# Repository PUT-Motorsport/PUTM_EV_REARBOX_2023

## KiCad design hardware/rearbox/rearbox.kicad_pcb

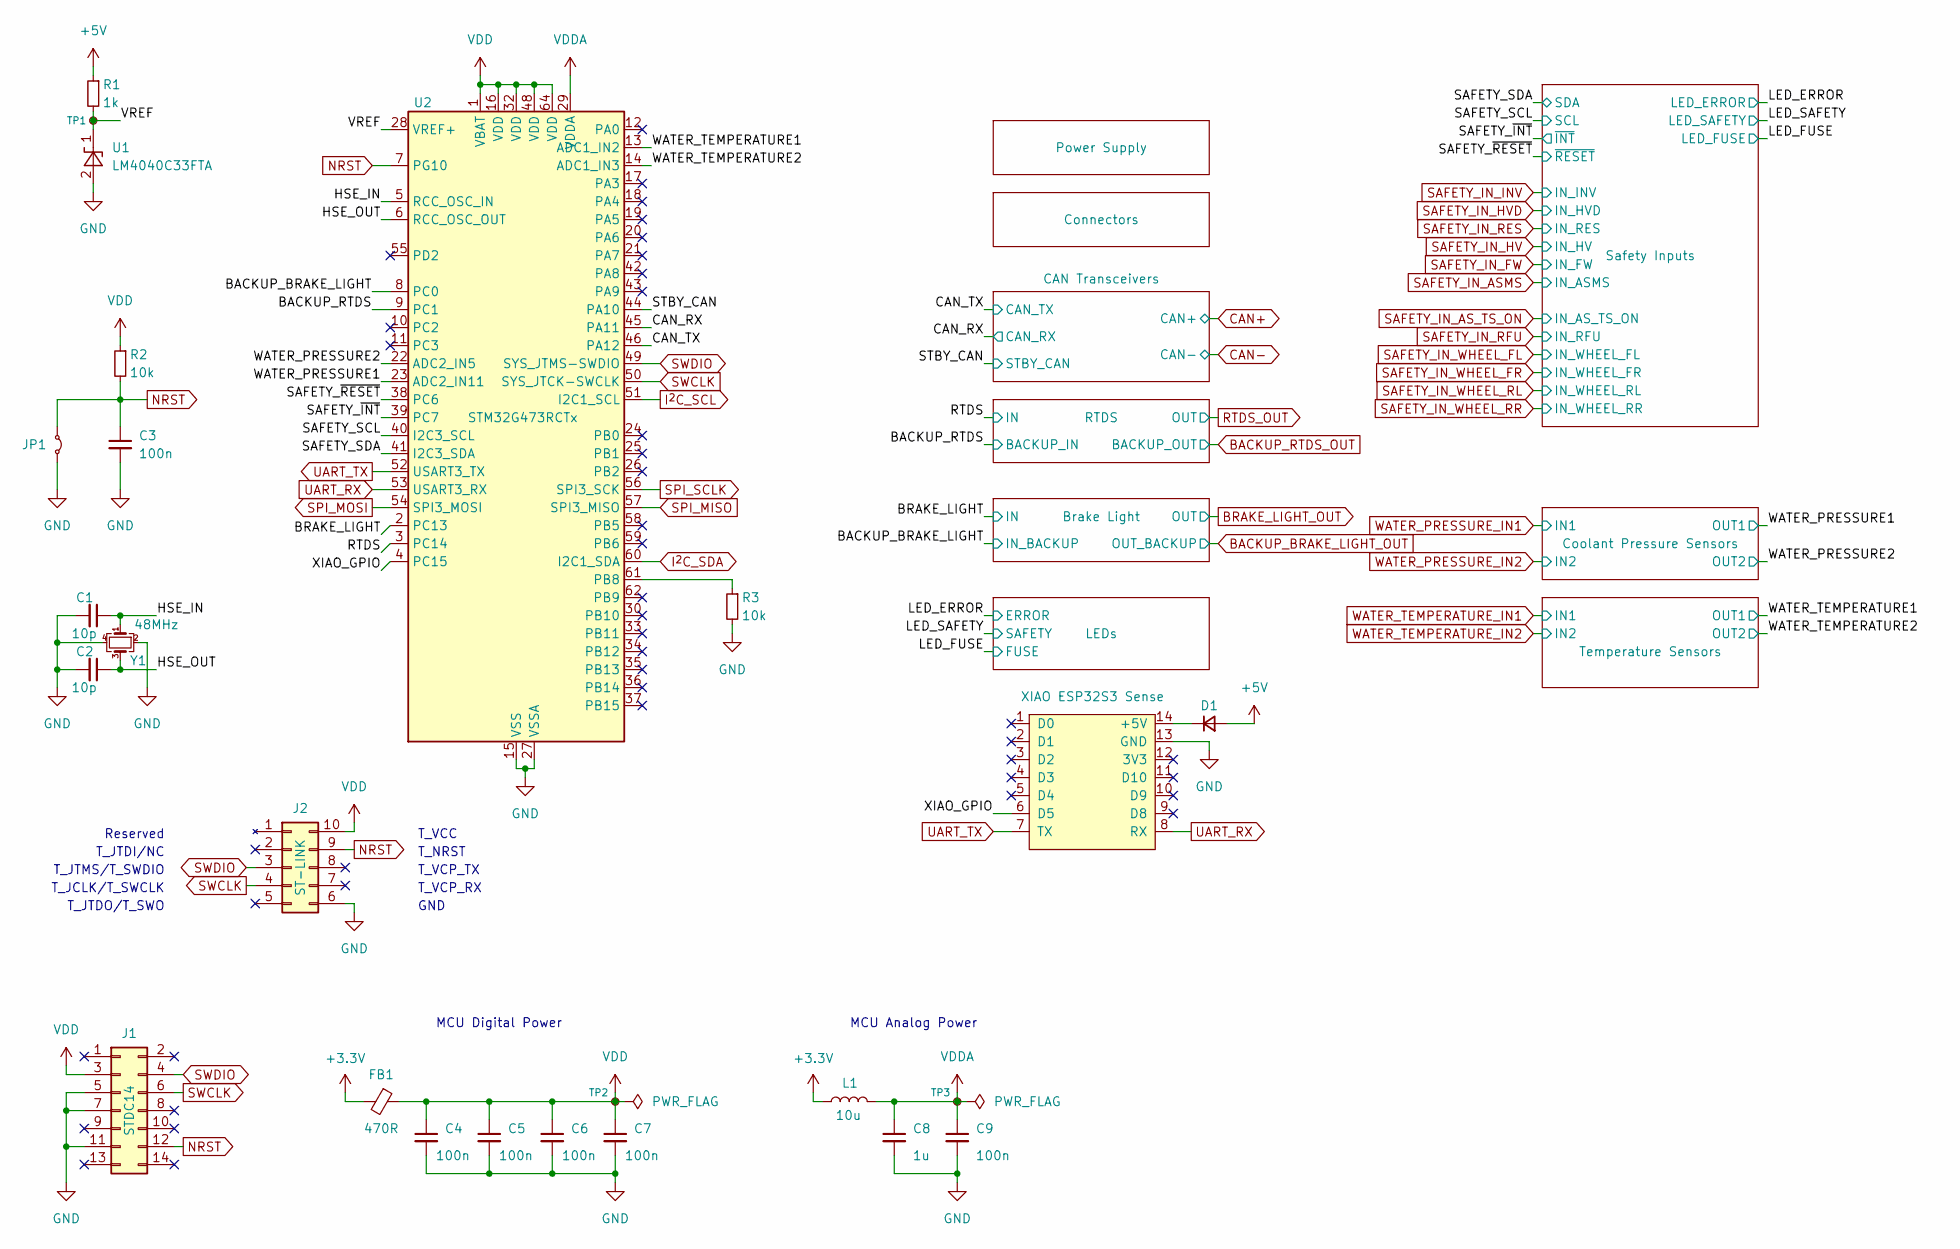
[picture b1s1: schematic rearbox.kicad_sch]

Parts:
C1, C2: 10p; C_0603_1608Metric
C3, C4, C5, C6, C7, C9: 100n; C_0603_1608Metric
C8: 1u; C_0603_1608Metric
D1: NSVRB751V40T1G; D_SOD-323_HandSoldering; Mouser Part Number 863-NSVRB751V40T1G
FB1: 470R; L_0603_1608Metric
J1: STDC14; PinHeader_2x07_P1.27mm_Vertical_SMD
J2: ST-LINK; STLINK-V3MINIE
J5: XIAO ESP32S3 Sense; XIAO-ESP32S3-DIP
JP1: Jumper_2_Small_Bridged; SolderJumper-2_P1.3mm_Open_TrianglePad1.0x1.5mm
L1: 10u; L_0603_1608Metric
R1: 1k; R_0603_1608Metric
R2, R3: 10k; R_0603_1608Metric
TP1, TP2, TP3: TestPoint_Small; TestPoint_Pad_D1.0mm
U1: LM4040C33FTA; SOT-23
U2: STM32G473RCTx; LQFP-64_10x10mm_P0.5mm
Y1: 48MHz; Crystal_SMD_Abracon_ABM8G-4Pin_3.2x2.5mm

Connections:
+3.3V: FB1.2, L1.1; also elsewhere on the board
+5V: D1.2 (A), R1.1; also elsewhere on the board
/BACKUP_BRAKE_LIGHT: U2.8 (PC0); also elsewhere on the board
/BACKUP_RTDS: U2.9 (PC1); also elsewhere on the board
/BRAKE_LIGHT: U2.2 (PC13); also elsewhere on the board
/CAN_RX: U2.45 (PA11); also elsewhere on the board
/CAN_TX: U2.46 (PA12); also elsewhere on the board
/HSE_IN: C1.1, U2.5 (RCC_OSC_IN), Y1.1
/HSE_OUT: C2.1, U2.6 (RCC_OSC_OUT), Y1.3
/RTDS: U2.3 (PC14); also elsewhere on the board
/SAFETY_SCL: U2.40 (I2C3_SCL); also elsewhere on the board
/SAFETY_SDA: U2.41 (I2C3_SDA); also elsewhere on the board
/SAFETY_~INT: U2.39 (PC7); also elsewhere on the board
/SAFETY_~RESET: U2.38 (PC6); also elsewhere on the board
/STBY_CAN: U2.44 (PA10); also elsewhere on the board
/VREF: R1.2, TP1.1, U1.1 (K), U2.28 (VREF+)
/WATER_PRESSURE1: U2.23 (ADC2_IN11); also elsewhere on the board
/WATER_PRESSURE2: U2.22 (ADC2_IN5); also elsewhere on the board
/WATER_TEMPERATURE1: U2.13 (ADC1_IN2); also elsewhere on the board
/WATER_TEMPERATURE2: U2.14 (ADC1_IN3); also elsewhere on the board
/XIAO_GPIO: J5.6 (D5), U2.4 (PC15)
GND: C1.2, C2.2, C3.2, C4.2, C5.2, C6.2, C7.2, C8.2, C9.2, J1.5, J1.7, J1.11, J2.6 (GND), J5.13 (GND), JP1.2 (B), R3.2, U1.2 (A), U2.15 (VSS), U2.27 (VSSA), U2.31 (VSS), U2.47 (VSS), U2.63 (VSS), Y1.2, Y1.4; also elsewhere on the board
I^{2}C_SCL: U2.51 (I2C1_SCL); also elsewhere on the board
I^{2}C_SDA: U2.60 (I2C1_SDA); also elsewhere on the board
NRST: C3.1, J1.12, J2.9 (T_NRST), JP1.1 (A), R2.2, U2.7 (PG10)
unnamed: D1.1 (K), J5.14 (+5V)
unnamed: R3.1, U2.61 (PB8)
SPI_MISO: U2.57 (SPI3_MISO); also elsewhere on the board
SPI_MOSI: U2.54 (SPI3_MOSI); also elsewhere on the board
SPI_SCLK: U2.56 (SPI3_SCK); also elsewhere on the board
SWCLK: J1.6, J2.4 (T_JCLK/T_SWCLK), U2.50 (SYS_JTCK-SWCLK)
SWDIO: J1.4, J2.3 (T_JTMS/T_SWDIO), U2.49 (SYS_JTMS-SWDIO)
UART_RX: J5.8 (RX), U2.53 (USART3_RX); also elsewhere on the board
UART_TX: J5.7 (TX), U2.52 (USART3_TX); also elsewhere on the board
VDD: C4.1, C5.1, C6.1, C7.1, FB1.1, J1.3, J2.10 (T_VCC), R2.1, TP2.1, U2.1 (VBAT), U2.16 (VDD), U2.32 (VDD), U2.48 (VDD), U2.64 (VDD)
VDDA: C8.1, C9.1, L1.2, TP3.1, U2.29 (VDDA)

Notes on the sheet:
T_JCLK/T_SWCLK
T_JTMS/T_SWDIO
MCU Analog Power
T_JTDI/NC
T_VCC
T_JTDO/T_SWO
T_NRST
Reserved
T_VCP_RX
T_VCP_TX
GND
MCU Digital Power

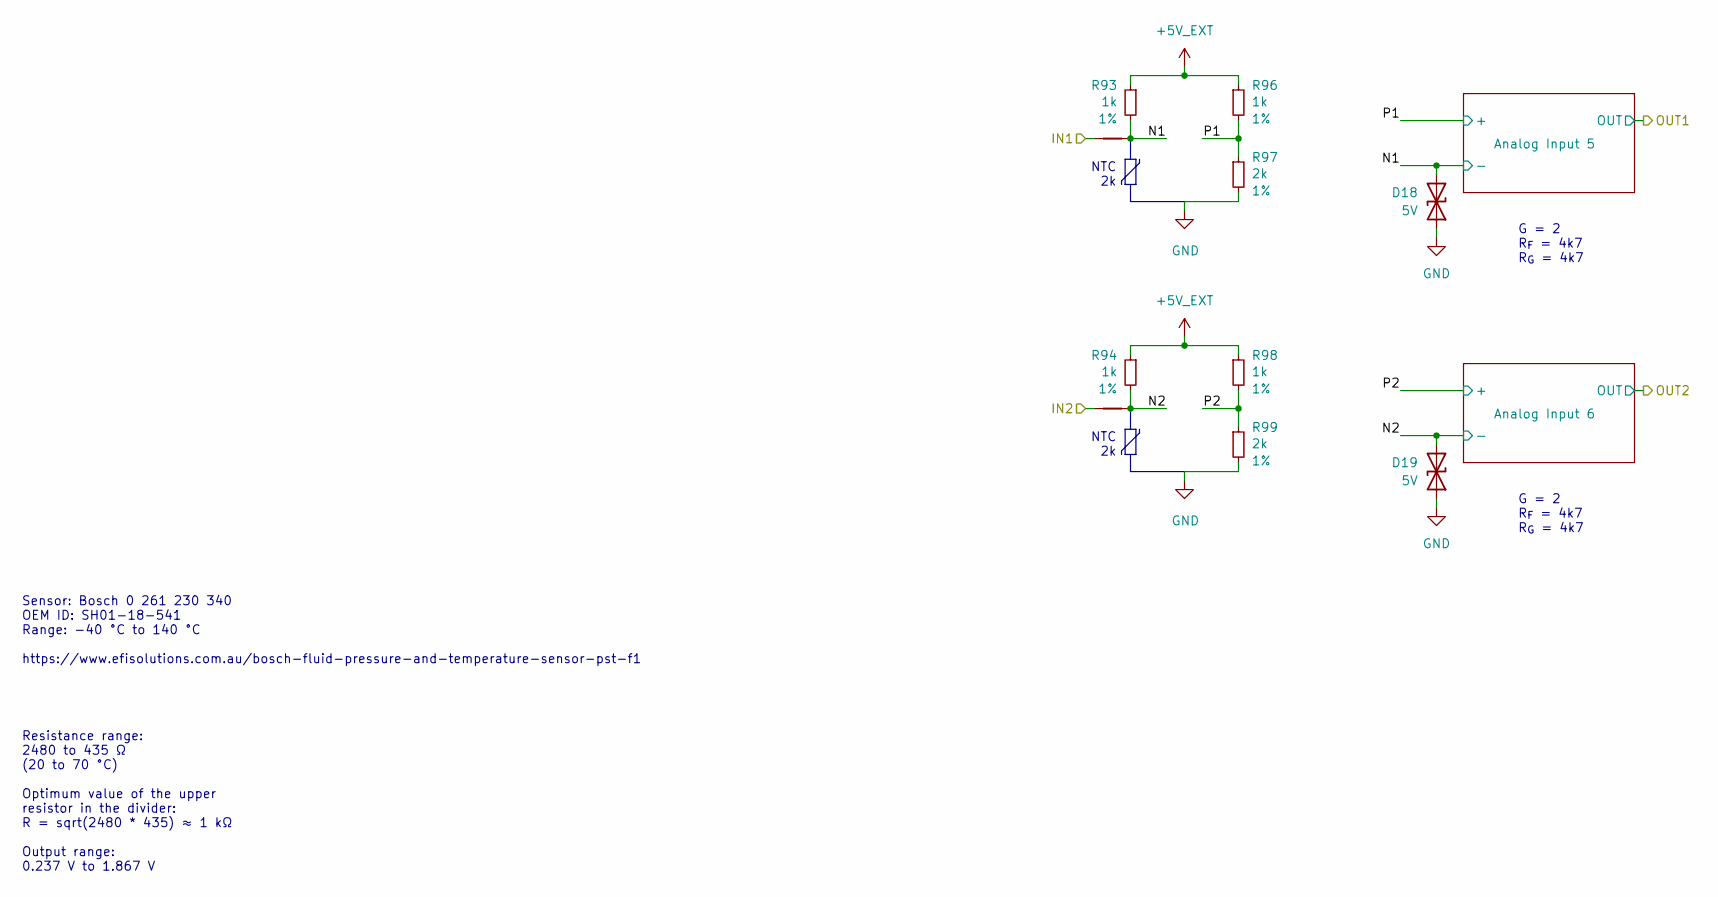
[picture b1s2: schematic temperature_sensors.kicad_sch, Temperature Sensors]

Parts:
D18, D19: 5V; D_SOD-523
NT1, NT2: NetTie_2; NetTie-2_SMD_Pad0.2mm
R93, R94, R96, R98: 1k; R_0603_1608Metric; Tolerance 1%
R97, R99: 2k; R_0603_1608Metric; Tolerance 1%

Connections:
+5V_EXT: R93.1, R94.1, R96.1, R98.1; also elsewhere on the board
/Temperature Sensors/N1: D18.2 (A2), NT1.2, R93.2; also elsewhere on the board
/Temperature Sensors/N2: D19.2 (A2), NT2.2, R94.2; also elsewhere on the board
/Temperature Sensors/P1: R96.2, R97.1; also elsewhere on the board
/Temperature Sensors/P2: R98.2, R99.1; also elsewhere on the board
GND: D18.1 (A1), D19.1 (A1), R97.2, R99.2; also elsewhere on the board
WATER_TEMPERATURE_IN1: NT1.1; also elsewhere on the board
WATER_TEMPERATURE_IN2: NT2.1; also elsewhere on the board

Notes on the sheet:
G = 2 R_{F} = 4k7 R_{G} = 4k7
NTC 2k
Resistance range: 2480 to 435 Ω (20 to 70 °C) Optimum value of the upper resistor in the divider: R = sqrt(2480 * 435) ≈ 1 kΩ Output range: 0.237 V to 1.867 V
Sensor: Bosch 0 261 230 340 OEM ID: SH01-18-541 Range: -40 °C to 140 °C https://www.efisolutions.com.au/bosch-fluid-pressure-and-temperature-sensor-pst-f1

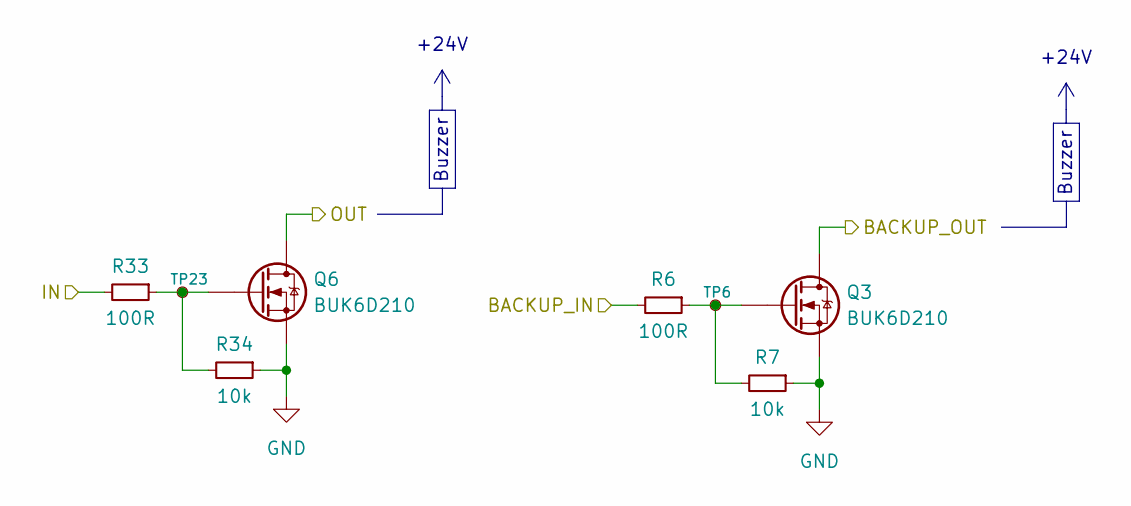
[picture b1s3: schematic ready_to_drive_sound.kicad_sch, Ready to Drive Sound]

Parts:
Q3, Q6: BUK6D210; Diodes_UDFN2020-6_Type-F
R6, R33: 100R; R_0603_1608Metric
R7, R34: 10k; R_0603_1608Metric
TP6, TP23: TestPoint_Small; TestPoint_Pad_D1.0mm

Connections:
/BACKUP_RTDS: R6.2; also elsewhere on the board
/RTDS: R33.2; also elsewhere on the board
BACKUP_RTDS_OUT: Q3.1 (D), Q3.2 (D), Q3.5 (D), Q3.6 (D), Q3.7 (D); also elsewhere on the board
GND: Q3.4 (S), Q3.8 (S), Q6.4 (S), Q6.8 (S), R7.1, R34.1; also elsewhere on the board
unnamed: Q3.3 (G), R6.1, R7.2, TP6.1
unnamed: Q6.3 (G), R33.1, R34.2, TP23.1
RTDS_OUT: Q6.1 (D), Q6.2 (D), Q6.5 (D), Q6.6 (D), Q6.7 (D); also elsewhere on the board

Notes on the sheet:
+24V
Buzzer

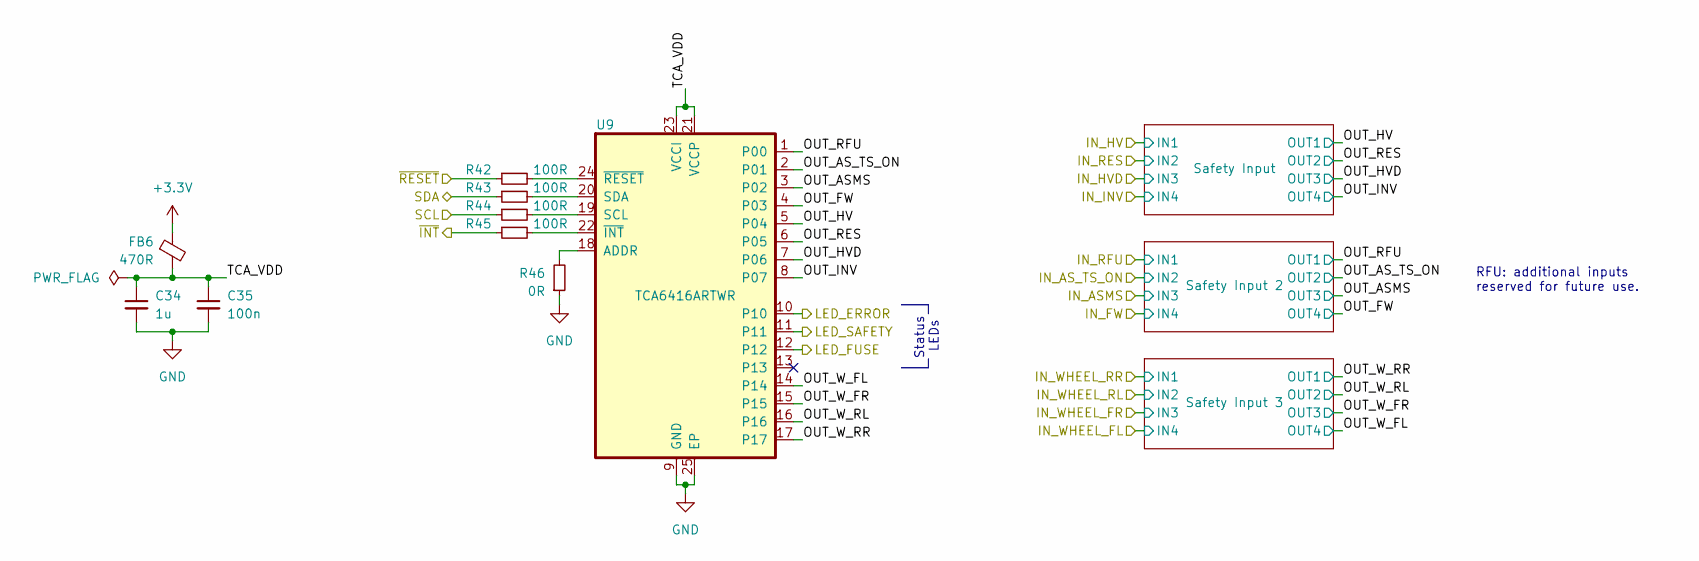
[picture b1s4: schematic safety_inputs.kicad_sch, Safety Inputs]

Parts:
C34: 1u; C_0603_1608Metric
C35: 100n; C_0603_1608Metric
FB6: 470R; L_0603_1608Metric
R42, R43, R44, R45: 100R; R_0603_1608Metric
R46: 0R; R_0603_1608Metric
U9: TCA6416ARTWR; QFN50P400X400X80-25N

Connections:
+3.3V: FB6.1; also elsewhere on the board
/LED_ERROR: U9.10; also elsewhere on the board
/LED_FUSE: U9.12; also elsewhere on the board
/LED_SAFETY: U9.11; also elsewhere on the board
/SAFETY_SCL: R44.1; also elsewhere on the board
/SAFETY_SDA: R43.1; also elsewhere on the board
/SAFETY_~INT: R45.1; also elsewhere on the board
/SAFETY_~RESET: R42.1; also elsewhere on the board
/Safety Inputs/OUT_ASMS: U9.3 (P02); also elsewhere on the board
/Safety Inputs/OUT_AS_TS_ON: U9.2 (P01); also elsewhere on the board
/Safety Inputs/OUT_FW: U9.4 (P03); also elsewhere on the board
/Safety Inputs/OUT_HV: U9.5 (P04); also elsewhere on the board
/Safety Inputs/OUT_HVD: U9.7 (P06); also elsewhere on the board
/Safety Inputs/OUT_INV: U9.8 (P07); also elsewhere on the board
/Safety Inputs/OUT_RES: U9.6 (P05); also elsewhere on the board
/Safety Inputs/OUT_RFU: U9.1 (P00); also elsewhere on the board
/Safety Inputs/OUT_W_FL: U9.14; also elsewhere on the board
/Safety Inputs/OUT_W_FR: U9.15; also elsewhere on the board
/Safety Inputs/OUT_W_RL: U9.16; also elsewhere on the board
/Safety Inputs/OUT_W_RR: U9.17; also elsewhere on the board
/Safety Inputs/TCA_VDD: C34.1, C35.1, FB6.2, U9.21 (VCCP), U9.23 (VCCI)
GND: C34.2, C35.2, R46.1, U9.9 (GND), U9.25 (EP); also elsewhere on the board
unnamed: R46.2, U9.18 (ADDR)
unnamed: R44.2, U9.19 (SCL)
unnamed: R43.2, U9.20 (SDA)
unnamed: R45.2, U9.22 (~INT)
unnamed: R42.2, U9.24 (~RESET)

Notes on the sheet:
Status LEDs
RFU: additional inputs reserved for future use.

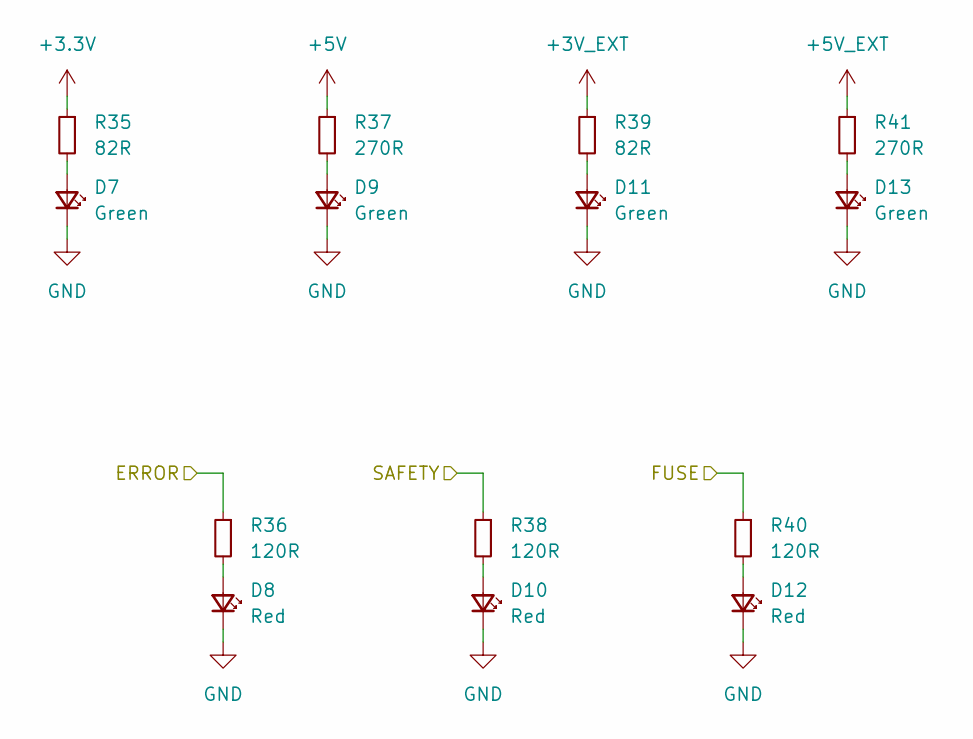
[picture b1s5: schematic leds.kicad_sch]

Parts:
D7, D9, D11, D13: Green; LED_0603_1608Metric
D8, D10, D12: Red; LED_0603_1608Metric
R35, R39: 82R; R_0603_1608Metric
R36, R38, R40: 120R; R_0603_1608Metric
R37, R41: 270R; R_0603_1608Metric

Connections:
+3.3V: R35.1; also elsewhere on the board
+3V_EXT: R39.1; also elsewhere on the board
+5V: R37.1; also elsewhere on the board
+5V_EXT: R41.1; also elsewhere on the board
/LED_ERROR: R36.1; also elsewhere on the board
/LED_FUSE: R40.1; also elsewhere on the board
/LED_SAFETY: R38.1; also elsewhere on the board
GND: D7.1 (K), D8.1 (K), D9.1 (K), D10.1 (K), D11.1 (K), D12.1 (K), D13.1 (K); also elsewhere on the board
unnamed: D7.2 (A), R35.2
unnamed: D8.2 (A), R36.2
unnamed: D9.2 (A), R37.2
unnamed: D10.2 (A), R38.2
unnamed: D11.2 (A), R39.2
unnamed: D12.2 (A), R40.2
unnamed: D13.2 (A), R41.2

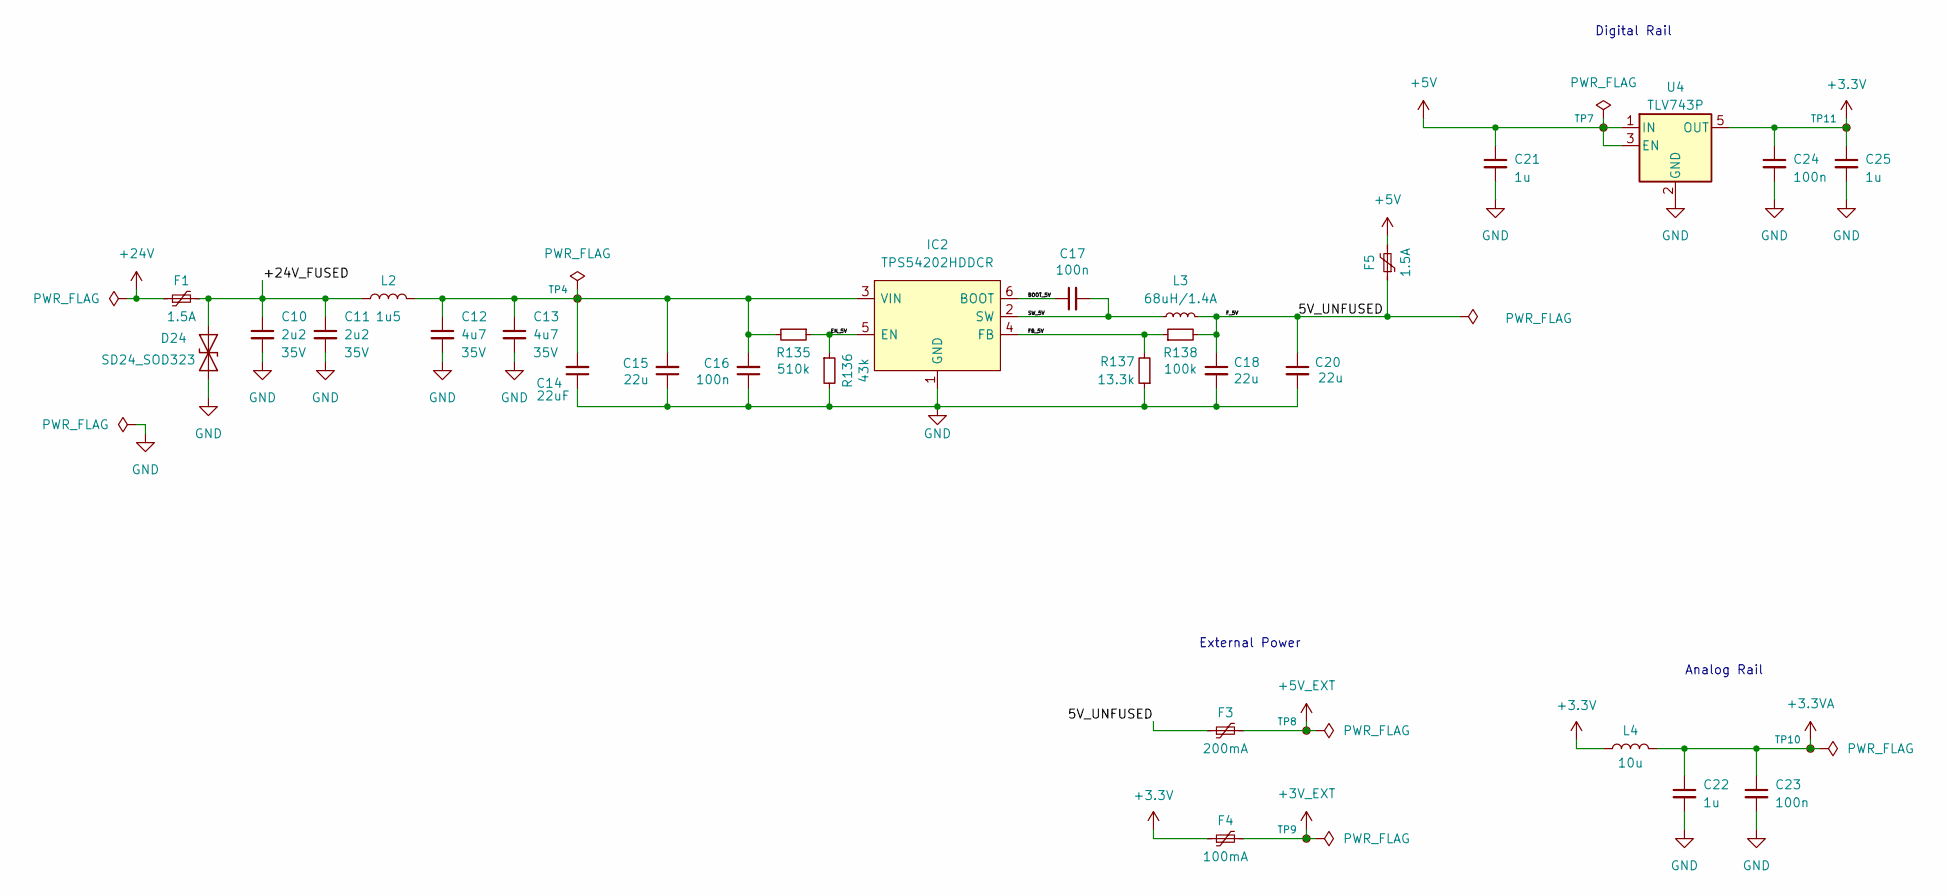
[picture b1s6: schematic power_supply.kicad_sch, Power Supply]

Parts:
C10, C11: 2u2; C_0805_2012Metric; Rated Voltage 35V
C12, C13: 4u7; C_0805_2012Metric; Rated Voltage 35V
C14: 22uF; C_0805_2012Metric; Manufacturer_Part_Number CL21A107MQYNNWE; Mouser Part Number 810-C2012X5R1V226MAC
C15, C18, C20: 22u; C_0805_2012Metric; Manufacturer_Part_Number CL21A107MQYNNWE; Mouser Part Number 810-C2012X5R1V226MAC
C16, C17: 100n; C_0603_1608Metric; Manufacturer_Part_Number C0603C104J3RACTU; Mouser Part Number --
C21, C22, C25: 1u; C_0603_1608Metric
C23, C24: 100n; C_0603_1608Metric
D24: SD24_SOD323; D_SOD-323
F1, F5: 1.5A; Fuse_1812_4532Metric
F3: 200mA; Fuse_1812_4532Metric
F4: 100mA; Fuse_1812_4532Metric
IC2: TPS54202HDDCR; SOT-23-6; Mouser Part Number 595-TPS54202HDDCR
L2: 1u5; L_Abracon_ASPI-4030S
L3: 68uH/1.4A; L_TDK_VLS6045EX_VLS6045AF; Mouser Part Number 810-VLS6045EX-680M
L4: 10u; L_0603_1608Metric
R135: 510k; R_0603_1608Metric; Manufacturer_Part_Number RT0603DRD07510KL; Mouser Part Number 603-RT0603DRD07510KL
R136: 43k; R_0603_1608Metric; Manufacturer_Part_Number RT0603DRD07510KL; Mouser Part Number 603-RT0603DRD07510KL
R137: 13.3k; R_0603_1608Metric; Manufacturer_Part_Number RT0603DRE0713K3L; Mouser Part Number 603-RT0603DRE0713K3L
R138: 100k; R_0603_1608Metric; Manufacturer_Part_Number RT0603DRE07100KL; Mouser Part Number --
TP4, TP7, TP8, TP9, TP10, TP11: TestPoint_Small; TestPoint_Pad_D1.0mm
U4: TLV743P; SOT-23-5

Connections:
+3.3V: C24.1, C25.1, F4.1, L4.1, TP11.1, U4.5 (OUT); also elsewhere on the board
+3.3VA: C22.1, C23.1, L4.2, TP10.1; also elsewhere on the board
+3V_EXT: F4.2, TP9.1; also elsewhere on the board
+5V: C21.1, F5.2, TP7.1, U4.1 (IN), U4.3 (EN); also elsewhere on the board
+5V_EXT: F3.2, TP8.1; also elsewhere on the board
+24V: F1.1; also elsewhere on the board
/Power Supply/5V_UNFUSED: C18.1, C20.1, F3.1, F5.1, L3.2, R138.2
/Power Supply/+24V_FUSED: C10.1, C11.1, D24.2 (A2), F1.2, L2.1
/Power Supply/BOOT_5V: C17.1, IC2.6 (BOOT)
/Power Supply/EN_5V: IC2.5 (EN), R135.1, R136.1
/Power Supply/FB_5V: IC2.4 (FB), R137.2, R138.1
/Power Supply/SW_5V: C17.2, IC2.2 (SW), L3.1
GND: C10.2, C11.2, C12.2, C13.2, C14.1, C15.1, C16.1, C18.2, C20.2, C21.2, C22.2, C23.2, C24.2, C25.2, D24.1 (A1), IC2.1 (GND), R136.2, R137.1, U4.2 (GND); also elsewhere on the board
unnamed: C12.1, C13.1, C14.2, C15.2, C16.2, IC2.3 (VIN), L2.2, R135.2, TP4.1

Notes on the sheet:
Analog Rail
Digital Rail
External Power

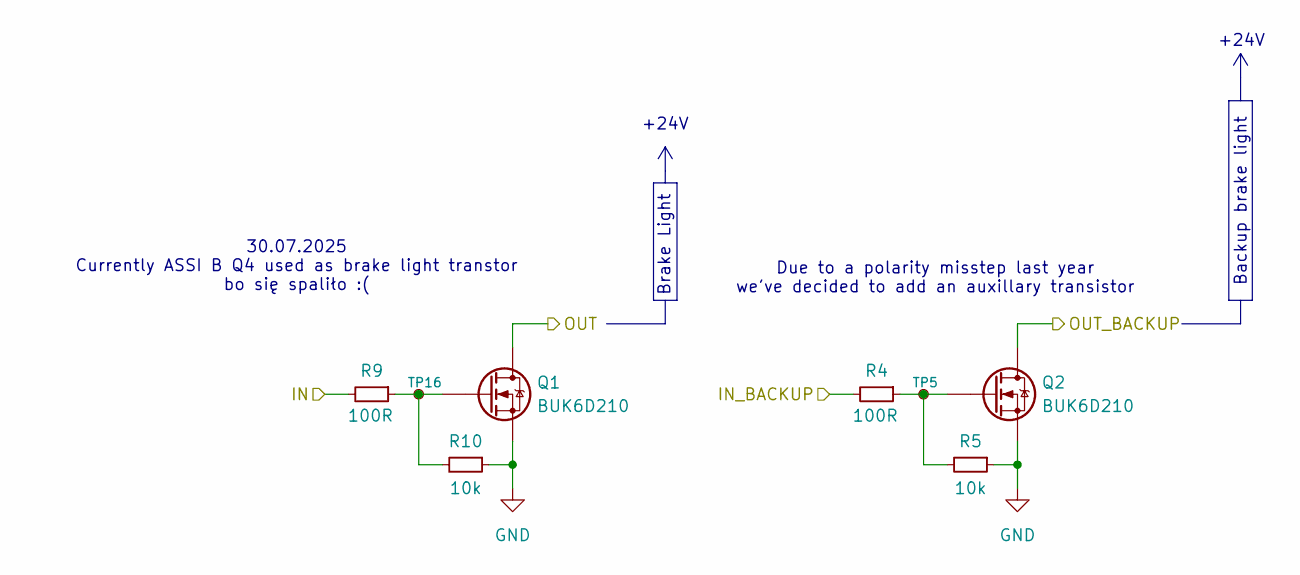
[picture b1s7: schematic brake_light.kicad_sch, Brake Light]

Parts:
Q1, Q2: BUK6D210; Diodes_UDFN2020-6_Type-F
R4, R9: 100R; R_0603_1608Metric
R5, R10: 10k; R_0603_1608Metric
TP5, TP16: TestPoint_Small; TestPoint_Pad_D1.0mm

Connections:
/BACKUP_BRAKE_LIGHT: R4.2; also elsewhere on the board
/BRAKE_LIGHT: R9.2; also elsewhere on the board
BACKUP_BRAKE_LIGHT_OUT: Q2.1 (D), Q2.2 (D), Q2.5 (D), Q2.6 (D), Q2.7 (D); also elsewhere on the board
BRAKE_LIGHT_OUT: Q1.1 (D), Q1.2 (D), Q1.5 (D), Q1.6 (D), Q1.7 (D); also elsewhere on the board
GND: Q1.4 (S), Q1.8 (S), Q2.4 (S), Q2.8 (S), R5.1, R10.1; also elsewhere on the board
unnamed: Q1.3 (G), R9.1, R10.2, TP16.1
unnamed: Q2.3 (G), R4.1, R5.2, TP5.1

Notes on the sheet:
30.07.2025 Currently ASSI B Q4 used as brake light transtor bo się spaliło :(
Brake Light
+24V
Due to a polarity misstep last year we've decided to add an auxillary transistor
Backup brake light

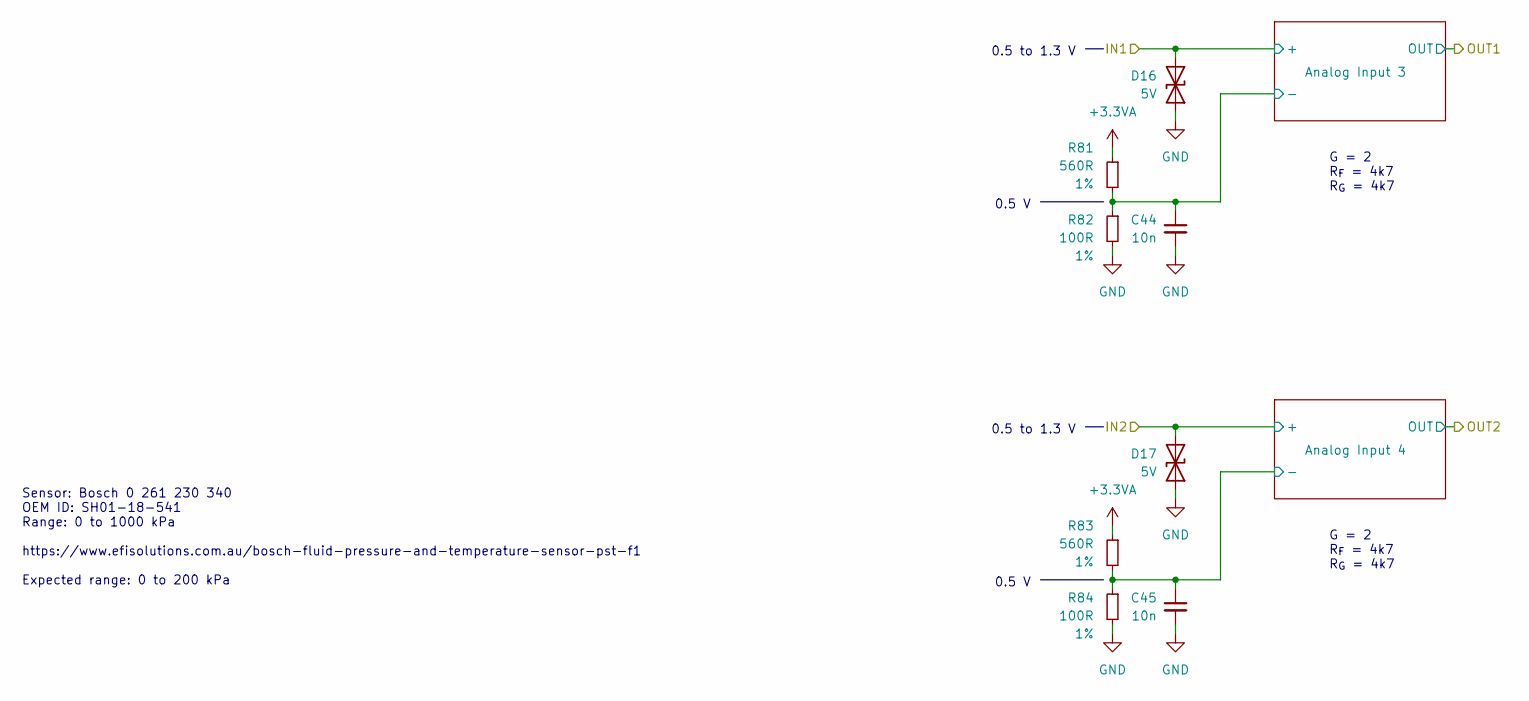
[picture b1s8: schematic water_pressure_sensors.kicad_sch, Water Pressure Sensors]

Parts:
C44, C45: 10n; C_0603_1608Metric
D16, D17: 5V; D_SOD-523
R81, R83: 560R; R_0603_1608Metric; Tolerance 1%
R82, R84: 100R; R_0603_1608Metric; Tolerance 1%

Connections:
+3.3VA: R81.1, R83.1; also elsewhere on the board
/Coolant Pressure Sensors/Analog Input 3/-: C44.1, R81.2, R82.1; also elsewhere on the board
/Coolant Pressure Sensors/Analog Input 4/-: C45.1, R83.2, R84.1; also elsewhere on the board
GND: C44.2, C45.2, D16.1 (A1), D17.1 (A1), R82.2, R84.2; also elsewhere on the board
WATER_PRESSURE_IN1: D16.2 (A2); also elsewhere on the board
WATER_PRESSURE_IN2: D17.2 (A2); also elsewhere on the board

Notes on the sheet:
0.5 V
0.5 to 1.3 V
G = 2 R_{F} = 4k7 R_{G} = 4k7
Sensor: Bosch 0 261 230 340 OEM ID: SH01-18-541 Range: 0 to 1000 kPa https://www.efisolutions.com.au/bosch-fluid-pressure-and-temperature-sensor-pst-f1 Expected range: 0 to 200 kPa

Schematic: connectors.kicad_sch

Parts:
J3: Conn_02x28_Top_Bottom; PinHeader_2x28_P2.00mm_Horizontal
J4: Auxiliary; PinHeader_2x05_P1.27mm_Vertical_SMD

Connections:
+3.3V: J4.2; also elsewhere on the board
+3V_EXT: J3.41; also elsewhere on the board
+5V: J4.1; also elsewhere on the board
+5V_EXT: J3.21; also elsewhere on the board
+24V: J3.1, J3.2, J3.3, J3.4, J3.5, J3.6; also elsewhere on the board
BACKUP_BRAKE_LIGHT_OUT: J3.47; also elsewhere on the board
BACKUP_RTDS_OUT: J3.53; also elsewhere on the board
BRAKE_LIGHT_OUT: J3.49; also elsewhere on the board
CAN+: J3.15; also elsewhere on the board
CAN-: J3.16; also elsewhere on the board
GND: J3.50, J3.51, J3.52, J3.54, J3.56, J4.9; also elsewhere on the board
I^{2}C_SCL: J4.4; also elsewhere on the board
I^{2}C_SDA: J4.10; also elsewhere on the board
RTDS_OUT: J3.55; also elsewhere on the board
SAFETY_IN_ASMS: J3.28; also elsewhere on the board
SAFETY_IN_AS_TS_ON: J3.30; also elsewhere on the board
SAFETY_IN_FW: J3.26; also elsewhere on the board
SAFETY_IN_HV: J3.24; also elsewhere on the board
SAFETY_IN_HVD: J3.20; also elsewhere on the board
SAFETY_IN_INV: J3.18; also elsewhere on the board
SAFETY_IN_RES: J3.22; also elsewhere on the board
SAFETY_IN_RFU: J3.32; also elsewhere on the board
SAFETY_IN_WHEEL_FL: J3.34; also elsewhere on the board
SAFETY_IN_WHEEL_FR: J3.36; also elsewhere on the board
SAFETY_IN_WHEEL_RL: J3.38; also elsewhere on the board
SAFETY_IN_WHEEL_RR: J3.40; also elsewhere on the board
SPI_MISO: J4.7; also elsewhere on the board
SPI_MOSI: J4.5; also elsewhere on the board
SPI_SCLK: J4.8; also elsewhere on the board
UART_RX: J4.6; also elsewhere on the board
UART_TX: J4.3; also elsewhere on the board
WATER_PRESSURE_IN1: J3.27; also elsewhere on the board
WATER_PRESSURE_IN2: J3.29; also elsewhere on the board
WATER_TEMPERATURE_IN1: J3.33; also elsewhere on the board
WATER_TEMPERATURE_IN2: J3.31; also elsewhere on the board

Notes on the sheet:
CAN2-
PUMP_OUT2
PUMP_OUT1
ANALOG_IN_RFU2
FAN_OUT_L
LOAD_CELL_IN_R+
ASSI_OUT_G
FAN_OUT_R
POTENTIOMETER_IN_R
ANALOG_IN_RFU1
1: Signals with no connect flag are still on Connector but are not proccesed at this board
POTENTIOMETER_IN_L
LOAD_CELL_IN_L+
LOAD_CELL_IN_R-
ASSI_OUT_R
LOAD_CELL_IN_L-
CAN2+
MONO_TEMPERATURE_IN
Power for Sensors
Power for Load Cells

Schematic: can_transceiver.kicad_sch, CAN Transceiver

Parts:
C30, C31, C36: 100n; C_0603_1608Metric_Pad1.08x0.95mm_HandSolder
C32, C38: 47u; C_0603_1608Metric_Pad1.08x0.95mm_HandSolder
C33, C37: 10n; C_0603_1608Metric_Pad1.08x0.95mm_HandSolder
C39: 220n; C_0603_1608Metric_Pad1.08x0.95mm_HandSolder
D14: 5.3V/400W; SOT-23-3; Mouser Part Number 511-ESDA5V3L
FB2, FB3, FB4, FB5: 2K@100MHz; L_0805_2012Metric_Pad1.05x1.20mm_HandSolder
R14: 100K; R_0603_1608Metric_Pad0.98x0.95mm_HandSolder
U7: ADM3057ExRW; SOIC-20W_7.5x12.8mm_P1.27mm

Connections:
+3.3V: C31.1, FB5.2; also elsewhere on the board
+5V: C30.2, FB2.2; also elsewhere on the board
/CAN Transceivers/CAN Transceiver/GNDISO_CAN: C36.1, C37.2, C38.1, D14.3 (A), FB4.1, R14.1, U7.11 (GND2), U7.15 (GND2)
/CAN_RX: U7.5 (RXD); also elsewhere on the board
/CAN_TX: U7.7 (TXD); also elsewhere on the board
/STBY_CAN: U7.8 (STBY); also elsewhere on the board
CAN+: D14.1 (K), U7.14 (CANH); also elsewhere on the board
CAN-: D14.2 (K), U7.13 (CANL); also elsewhere on the board
GND: C30.1, C31.2, C32.1, C33.2, U7.1 (GND1), U7.2 (GND1), U7.9 (AUXIN), U7.10 (GND1); also elsewhere on the board
unnamed: C39.1, FB4.2, U7.18 (GNDISO), U7.20 (GNDISO)
unnamed: R14.2, U7.12 (RS)
unnamed: C32.2, FB2.1, U7.3 (VCC)
unnamed: C33.1, FB5.1, U7.4 (VIO)
unnamed: C36.2, C37.1, C38.2, FB3.1, U7.16 (VISOIN)
unnamed: C39.2, FB3.2, U7.19 (VISOOUT)

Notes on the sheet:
1* Slope control for 5 Mbps

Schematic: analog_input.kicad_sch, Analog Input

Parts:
C46, C47, C48, C49: 100n; C_0603_1608Metric
R85, R86: TBD; R_0603_1608Metric
R87, R88: 3k3; R_0603_1608Metric
TP32, TP33, TP34, TP35: TestPoint_Small; TestPoint_Pad_D1.0mm
U17: MCP6N11T-002; TDFN-8-1EP_3x2mm_P0.5mm_EP1.80x1.65mm
U18: MCP6001; SOT-23-5

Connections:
+3.3VA: C48.1, C49.1, U17.7 (V+), U17.8 (EN), U18.5 (V+); also elsewhere on the board
/Coolant Pressure Sensors/Analog Input 3/-: TP33.1, U17.2 (-); also elsewhere on the board
/WATER_PRESSURE1: C47.2, TP35.1, U18.1, U18.4 (-); also elsewhere on the board
GND: C46.2, C48.2, C49.2, R86.1, U17.4 (V-), U17.5 (RF), U17.9 (EP), U18.2 (V-); also elsewhere on the board
unnamed: C47.1, R87.2, R88.1
unnamed: R85.2, R87.1, TP34.1, U17.6
unnamed: R85.1, R86.2, U17.1 (FG)
unnamed: C46.1, R88.2, U18.3 (+)
WATER_PRESSURE_IN1: TP32.1, U17.3 (+); also elsewhere on the board

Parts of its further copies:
C50, C51, C52, C53, C54, C55, C56, C57, C58, C59, C60, C61: 100n; C_0603_1608Metric
R89, R90, R102, R103, R106, R107: TBD; R_0603_1608Metric
R91, R92, R104, R105, R108, R109: 3k3; R_0603_1608Metric
TP36, TP37, TP38, TP39, TP40, TP41, TP42, TP43, TP44, TP45, TP46, TP47: TestPoint_Small; TestPoint_Pad_D1.0mm
U19, U21, U23: MCP6N11T-002; TDFN-8-1EP_3x2mm_P0.5mm_EP1.80x1.65mm
U20, U22, U24: MCP6001; SOT-23-5

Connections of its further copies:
+3.3VA: C52.1, C53.1, C56.1, C57.1, C60.1, C61.1, U19.7 (V+), U19.8 (EN), U20.5 (V+), U21.7 (V+), U21.8 (EN), U22.5 (V+), U23.7 (V+), U23.8 (EN), U24.5 (V+); also elsewhere on the board
/Coolant Pressure Sensors/Analog Input 4/-: TP37.1, U19.2 (-); also elsewhere on the board
/Temperature Sensors/N1: TP41.1, U21.2 (-); also elsewhere on the board
/Temperature Sensors/N2: TP45.1, U23.2 (-); also elsewhere on the board
/Temperature Sensors/P1: TP40.1, U21.3 (+); also elsewhere on the board
/Temperature Sensors/P2: TP44.1, U23.3 (+); also elsewhere on the board
/WATER_PRESSURE2: C51.2, TP39.1, U20.1, U20.4 (-); also elsewhere on the board
/WATER_TEMPERATURE1: C55.2, TP43.1, U22.1, U22.4 (-); also elsewhere on the board
/WATER_TEMPERATURE2: C59.2, TP47.1, U24.1, U24.4 (-); also elsewhere on the board
GND: C50.2, C52.2, C53.2, C54.2, C56.2, C57.2, C58.2, C60.2, C61.2, R90.1, R103.1, R107.1, U19.4 (V-), U19.5 (RF), U19.9 (EP), U20.2 (V-), U21.4 (V-), U21.5 (RF), U21.9 (EP), U22.2 (V-), U23.4 (V-), U23.5 (RF), U23.9 (EP), U24.2 (V-); also elsewhere on the board
unnamed: C51.1, R91.2, R92.1
unnamed: C55.1, R104.2, R105.1
unnamed: C59.1, R108.2, R109.1
unnamed: R89.2, R91.1, TP38.1, U19.6
unnamed: R102.2, R104.1, TP42.1, U21.6
unnamed: R106.2, R108.1, TP46.1, U23.6
unnamed: R89.1, R90.2, U19.1 (FG)
unnamed: C50.1, R92.2, U20.3 (+)
unnamed: R102.1, R103.2, U21.1 (FG)
unnamed: C54.1, R105.2, U22.3 (+)
unnamed: R106.1, R107.2, U23.1 (FG)
unnamed: C58.1, R109.2, U24.3 (+)
WATER_PRESSURE_IN2: TP36.1, U19.3 (+); also elsewhere on the board

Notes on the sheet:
Anti-aliasing Filter
G = TBD
f_{c} ≈ 482 Hz
Instrumentation Amplifier

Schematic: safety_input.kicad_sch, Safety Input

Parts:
R47: 4k7; R_0603_1608Metric
R48, R51, R52: 2k; R_0603_1608Metric
R49, R50, R53, R54: 10k; R_0603_1608Metric
U10: TLP291-4; SOIC-16_4.55x10.3mm_P1.27mm

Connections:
+3.3V: R49.2, R50.2, R53.2, R54.2; also elsewhere on the board
/Safety Inputs/OUT_HV: R49.1, U10.16; also elsewhere on the board
/Safety Inputs/OUT_HVD: R53.1, U10.12; also elsewhere on the board
/Safety Inputs/OUT_INV: R54.1, U10.10; also elsewhere on the board
/Safety Inputs/OUT_RES: R50.1, U10.14; also elsewhere on the board
GND: U10.2, U10.4, U10.6, U10.8, U10.9, U10.11, U10.13, U10.15; also elsewhere on the board
unnamed: R47.2, U10.1
unnamed: R48.2, U10.3
unnamed: R51.2, U10.5
unnamed: R52.2, U10.7
SAFETY_IN_HV: R47.1; also elsewhere on the board
SAFETY_IN_HVD: R51.1; also elsewhere on the board
SAFETY_IN_INV: R52.1; also elsewhere on the board
SAFETY_IN_RES: R48.1; also elsewhere on the board

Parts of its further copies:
R55, R63: 4k7; R_0603_1608Metric
R56, R59, R60, R64, R67, R68: 2k; R_0603_1608Metric
R57, R58, R61, R62, R65, R66, R69, R70: 10k; R_0603_1608Metric
U11, U12: TLP291-4; SOIC-16_4.55x10.3mm_P1.27mm

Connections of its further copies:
+3.3V: R57.2, R58.2, R61.2, R62.2, R65.2, R66.2, R69.2, R70.2; also elsewhere on the board
/Safety Inputs/OUT_ASMS: R61.1, U11.12; also elsewhere on the board
/Safety Inputs/OUT_AS_TS_ON: R58.1, U11.14; also elsewhere on the board
/Safety Inputs/OUT_FW: R62.1, U11.10; also elsewhere on the board
/Safety Inputs/OUT_RFU: R57.1, U11.16; also elsewhere on the board
/Safety Inputs/OUT_W_FL: R70.1, U12.10; also elsewhere on the board
/Safety Inputs/OUT_W_FR: R69.1, U12.12; also elsewhere on the board
/Safety Inputs/OUT_W_RL: R66.1, U12.14; also elsewhere on the board
/Safety Inputs/OUT_W_RR: R65.1, U12.16; also elsewhere on the board
GND: U11.2, U11.4, U11.6, U11.8, U11.9, U11.11, U11.13, U11.15, U12.2, U12.4, U12.6, U12.8, U12.9, U12.11, U12.13, U12.15; also elsewhere on the board
unnamed: R55.2, U11.1
unnamed: R56.2, U11.3
unnamed: R59.2, U11.5
unnamed: R60.2, U11.7
unnamed: R63.2, U12.1
unnamed: R64.2, U12.3
unnamed: R67.2, U12.5
unnamed: R68.2, U12.7
SAFETY_IN_ASMS: R59.1; also elsewhere on the board
SAFETY_IN_AS_TS_ON: R56.1; also elsewhere on the board
SAFETY_IN_FW: R60.1; also elsewhere on the board
SAFETY_IN_RFU: R55.1; also elsewhere on the board
SAFETY_IN_WHEEL_FL: R68.1; also elsewhere on the board
SAFETY_IN_WHEEL_FR: R67.1; also elsewhere on the board
SAFETY_IN_WHEEL_RL: R64.1; also elsewhere on the board
SAFETY_IN_WHEEL_RR: R63.1; also elsewhere on the board
